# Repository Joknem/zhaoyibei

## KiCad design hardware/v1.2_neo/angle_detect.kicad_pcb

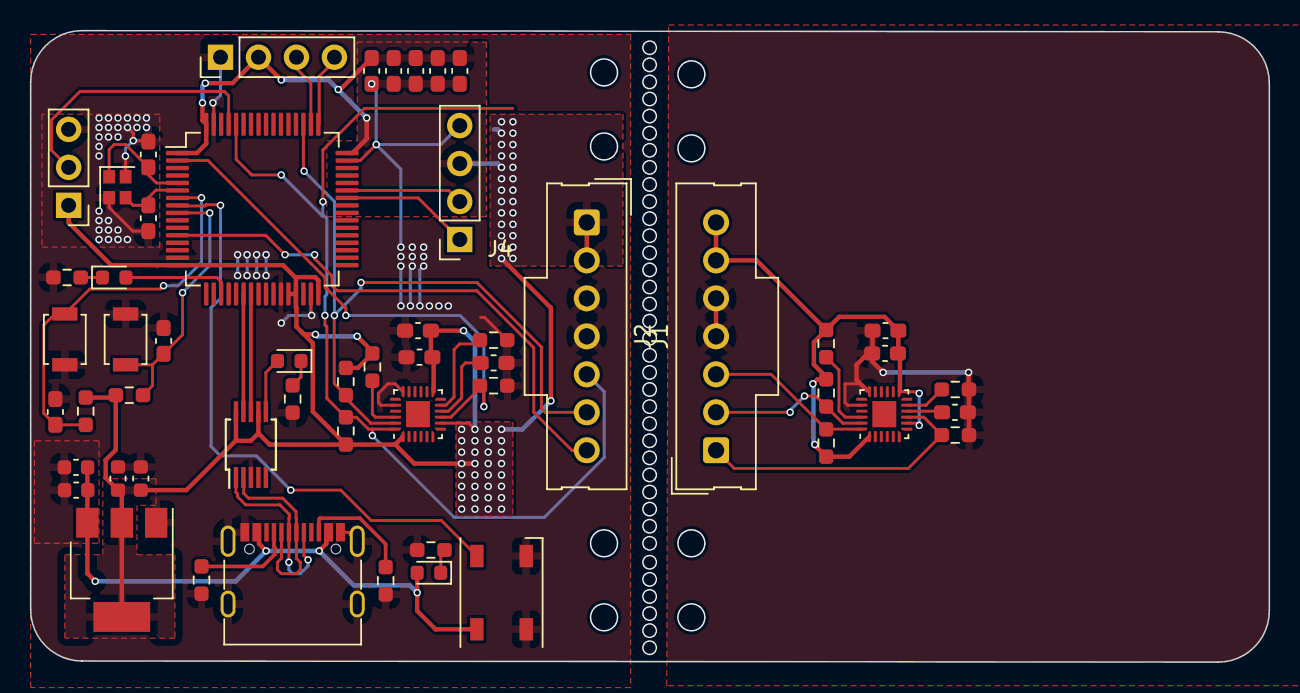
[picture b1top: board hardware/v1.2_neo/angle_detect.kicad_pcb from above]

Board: 2 copper layers, 82.9 x 42.2 mm, 54 parts (0 on the bottom side), 39 nets.

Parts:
C1, C16: 10nF; C_0603_1608Metric_Pad1.08x0.95mm_HandSolder
C2, C14, C15, C17, C18, C19: 0.1uF; C_0603_1608Metric_Pad1.08x0.95mm_HandSolder
C3, C6: 0.1uF; C_0603_1608Metric
C4, C5: 10uF; C_0603_1608Metric
C7, C8: 6.8pF; C_0603_1608Metric_Pad1.08x0.95mm_HandSolder
C9, C10, C11, C12: 100nF; C_0603_1608Metric_Pad1.08x0.95mm_HandSolder
C13: 4.7uF; C_0603_1608Metric_Pad1.08x0.95mm_HandSolder
D1: WS2812B; LED_WS2812B_PLCC4_5.0x5.0mm_P3.2mm
J1, J2: Conn_01x07; Molex_SL_171971-0007_1x07_P2.54mm_Vertical
J3: USB_C_Receptacle_USB2.0; USB_C_Receptacle_G-Switch_GT-USB-7010ASV
J4: IIC_OLED; PinSocket_1x04_P2.54mm_Vertical
J5: SWD; PinHeader_1x04_P2.54mm_Vertical
J6: Conn_01x03; PinHeader_1x03_P2.54mm_Vertical
R1, R2: 5.1k; R_0603_1608Metric_Pad0.98x0.95mm_HandSolder
R3, R4, R18: 500R; R_0603_1608Metric_Pad0.98x0.95mm_HandSolder
R5: 1k; R_0603_1608Metric_Pad0.98x0.95mm_HandSolder
R7, R8, R9, R10, R11, R12, R13, R14, R15, R16, R17: 10k; R_0603_1608Metric_Pad0.98x0.95mm_HandSolder
SW1: NRST_BUTTON; SW_SPST_B3U-1000P
SW2: USER_BUTTON; SW_SPST_B3U-1000P
U1: STM32G474RETx; LQFP-64_10x10mm_P0.5mm
U2, U3: MPU-9250; QFN-24-1EP_3x3mm_P0.4mm_EP1.75x1.6mm
U4: AMS1117-3.3; SOT-223-3_TabPin2
U5: CH340E; MSOP-10_3x3mm_P0.5mm
Y2: Crystal_GND24; Crystal_SMD_2016-4Pin_2.0x1.6mm
power_led1: LED; LED_0603_1608Metric
uart_led1: LED; LED_0603_1608Metric
user_led1: LED; LED_0603_1608Metric

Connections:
+3.3V: C5.1, C6.1, C9.1, C10.1, C11.1, C12.1, C13.1, C16.1, C18.1, J2.1, J2.2, J4.3, J5.2, J6.1, R5.1, R9.1, R11.2, R12.2, R13.2, U1.1 (VBAT), U1.16 (VDD), U1.28 (VREF+), U1.29 (VDDA), U1.32 (VDD), U1.48 (VDD), U1.64 (VDD), U3.1 (RESV_VDDIO), U3.8 (VDDIO), U3.13 (VDD), U4.2 (VO), U5.7 (VCC), U5.10 (V3)
+5V: C3.1, C4.1, D1.1 (VDD), J3.A4 (VBUS), J3.A9 (VBUS), J3.B4 (VBUS), J3.B9 (VBUS), U4.3 (VI), power_led1.2 (A)
/3.3V_B: C1.1, C2.1, J1.6, J1.7, R8.2, R10.2, R17.2, U2.1 (RESV_VDDIO), U2.8 (VDDIO), U2.13 (VDD)
/AD0: R14.2, U1.2 (PC13), U3.9 (AD0/MISO)
/AD1: J2.7, U1.12 (PA0)
/AD1_B: J1.1, R7.2, U2.9 (AD0/MISO)
/BOOT: J6.2, U1.61 (PB8)
/D+: J3.A6 (D+), J3.B6 (D+), U5.1 (UD+)
/D-: J3.A7 (D-), J3.B7 (D-), U5.2 (UD-)
/GND_B: C1.2, C2.2, C19.2, J1.4, J1.5, R7.1, R16.1, U2.18 (GND), U2.20 (RESV_GND)
/MPU_SCL: J2.6, R11.1, U1.51 (PA15), U3.23 (SCL/SCLK)
/MPU_SCL_B: J1.2, R8.1, U2.23 (SCL/SCLK)
/MPU_SDA: J2.5, R12.1, U1.60 (PB7), U3.24 (SDA/MOSI)
/MPU_SDA_B: J1.3, R10.1, U2.24 (SDA/MOSI)
/OLED_SCL: J4.2, U1.43 (PA9)
/OLED_SDA: J4.1, U1.42 (PA8)
/RX: U1.23 (PC5), U5.8 (TXD)
/SWCLK: J5.3, U1.50 (PA14)
/SWDIO: J5.4, U1.49 (PA13)
/TNOW: U5.6 (TNOW), uart_led1.2 (A)
/TX: U1.22 (PC4), U5.9 (RXD)
/USER_LED: U1.19 (PA5), user_led1.2 (A)
/rgb: D1.4 (DIN), U1.8 (PC0)
/user_button: C15.2, R9.2, SW2.1, U1.9 (PC1)
GND: C3.2, C4.2, C5.2, C6.2, C7.1, C8.1, C9.2, C10.2, C11.2, C12.2, C13.2, C14.2, C15.1, C16.2, C17.2, C18.2, D1.2 (DOUT), D1.3 (VSS), J2.3, J2.4, J3.A1 (GND), J3.A12 (GND), J3.B1 (GND), J3.B12 (GND), J3.S1 (SHIELD), J4.4, J5.1, J6.3, R1.2, R2.1, R3.2, R4.2, R14.1, R15.1, R18.2, SW1.2, SW2.2, U1.15 (VSS), U1.27 (VSSA), U1.31 (VSS), U1.47 (VSS), U1.63 (VSS), U3.18 (GND), U3.20 (RESV_GND), U4.1 (GND), U5.3 (GND), Y2.2, Y2.4
NRST: C14.1, R5.2, SW1.1, U1.7 (PG10)
unnamed: J3.A5 (CC1), R1.1
unnamed: J3.B5 (CC2), R2.2
unnamed: C7.2, U1.5 (PF0), Y2.1
unnamed: C8.2, U1.6 (PF1), Y2.3
unnamed: R16.2, U2.11 (FSYNC)
unnamed: C19.1, U2.10 (REGOUT)
unnamed: R17.1, U2.22 (~CS)
unnamed: R15.2, U3.11 (FSYNC)
unnamed: C17.1, U3.10 (REGOUT)
unnamed: R13.1, U3.22 (~CS)
unnamed: R3.1, power_led1.1 (K)
unnamed: R18.1, uart_led1.1 (K)
unnamed: R4.1, user_led1.1 (K)

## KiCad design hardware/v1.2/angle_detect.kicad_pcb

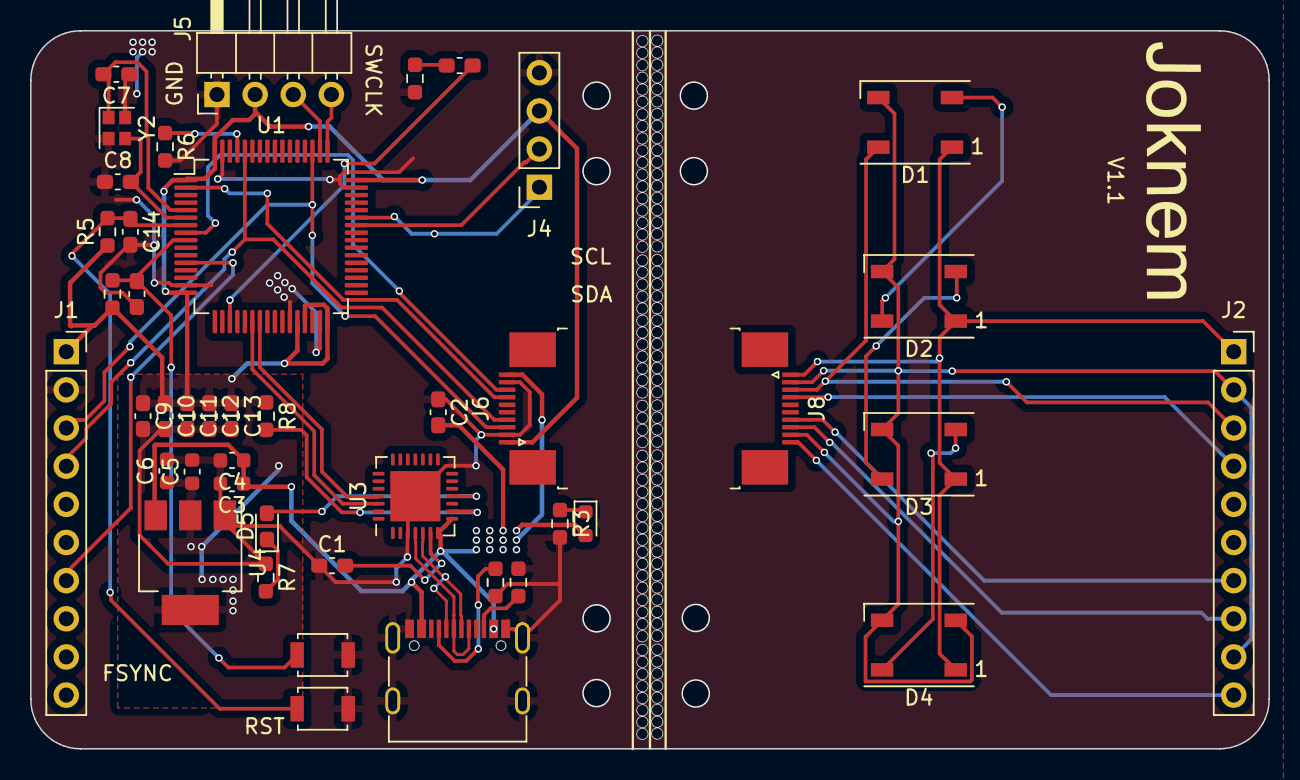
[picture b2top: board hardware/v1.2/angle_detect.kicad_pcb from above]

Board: 2 copper layers, 82.4 x 47.8 mm, 44 parts (0 on the bottom side), 40 nets.

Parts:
C1, C14, C15: 0.1uF; C_0603_1608Metric_Pad1.08x0.95mm_HandSolder
C2: 1uF; C_0603_1608Metric_Pad1.08x0.95mm_HandSolder
C3, C6: 0.1uF; C_0603_1608Metric
C4, C5: 10uF; C_0603_1608Metric
C7, C8: 6.8pF; C_0603_1608Metric_Pad1.08x0.95mm_HandSolder
C9, C10, C11, C12: 100nF; C_0603_1608Metric_Pad1.08x0.95mm_HandSolder
C13: 4.7uF; C_0603_1608Metric_Pad1.08x0.95mm_HandSolder
D1, D2, D3, D4: WS2812B; LED_WS2812B_PLCC4_5.0x5.0mm_P3.2mm
D5: uart_led; LED_0603_1608Metric_Pad1.05x0.95mm_HandSolder
J1: MPU_1; PinSocket_1x10_P2.54mm_Vertical
J2: MPU_2; PinSocket_1x10_P2.54mm_Vertical
J3: USB_C_Receptacle_USB2.0; USB_C_Receptacle_G-Switch_GT-USB-7010ASV
J4: IIC_OLED; PinSocket_1x04_P2.54mm_Vertical
J5: SWD; PinHeader_1x04_P2.54mm_Horizontal
J6: MPU_2_fpc1; TE_1-1734839-0_1x10-1MP_P0.5mm_Horizontal
J8: MPU_2_fpc2; TE_1-1734839-0_1x10-1MP_P0.5mm_Horizontal
R1, R2: 5.1k; R_0603_1608Metric_Pad0.98x0.95mm_HandSolder
R3, R4, R7: 500R; R_0603_1608Metric_Pad0.98x0.95mm_HandSolder
R5: 1k; R_0603_1608Metric_Pad0.98x0.95mm_HandSolder
R6, R9: 10k; R_0603_1608Metric_Pad0.98x0.95mm_HandSolder
R8: 4.7k; R_0603_1608Metric_Pad0.98x0.95mm_HandSolder
SW1: NRST_BUTTON; SW_SPST_B3U-1000P
SW2: USER_BUTTON; SW_SPST_B3U-1000P
U1: STM32G474RETx; LQFP-64_10x10mm_P0.5mm
U3: CP2102N-Axx-xQFN28; QFN-28-1EP_5x5mm_P0.5mm_EP3.35x3.35mm
U4: AMS1117-3.3; SOT-223-3_TabPin2
Y2: Crystal_GND24; Crystal_SMD_2016-4Pin_2.0x1.6mm
power_led1: LED; LED_0603_1608Metric
user_led1: LED; C_0603_1608Metric_Pad1.08x0.95mm_HandSolder

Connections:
+3.3V: C5.1, C6.1, C9.1, C10.1, C11.1, C12.1, C13.1, J1.1, J4.3, J5.2, J6.1, R5.1, R8.1, R9.1, U1.1 (VBAT), U1.16 (VDD), U1.28 (VREF+), U1.29 (VDDA), U1.32 (VDD), U1.48 (VDD), U1.64 (VDD), U4.2 (VO)
+5V: C2.2, C3.1, C4.1, J3.A4 (VBUS), J3.A9 (VBUS), J3.B4 (VBUS), J3.B9 (VBUS), J6.10, U3.7 (VREGIN), U3.8 (VBUS), U4.3 (VI), power_led1.2 (A)
/+3.3V_b: J2.10, J8.10
/+5V_b: D1.1 (VDD), D2.1 (VDD), D3.1 (VDD), D4.1 (VDD), J2.1, J8.1
/AD0: J1.7, U1.12 (PA0)
/AD1: J6.7, U1.2 (PC13)
/AD1_b: J2.4, J8.4
/BOOT: R6.1, U1.61 (PB8)
/D+: J3.A6 (D+), J3.B6 (D+), U3.4 (D+)
/D-: J3.A7 (D-), J3.B7 (D-), U3.5 (D-)
/GND_b: D1.3 (VSS), D2.3 (VSS), D3.3 (VSS), D4.2 (DOUT), D4.3 (VSS), J2.2, J2.9, J8.2, J8.9
/MPU_SCL: J1.3, J6.3, U1.51 (PA15)
/MPU_SCL_b: J2.8, J8.8
/MPU_SDA: J1.4, J6.4, U1.60 (PB7)
/MPU_SDA_b: J2.7, J8.7
/OLED_SCL: J4.2, U1.42 (PA8)
/OLED_SDA: J4.1, U1.43 (PA9)
/RX: U1.23 (PC5), U3.25 (RXD)
/SWCLK: J5.4, U1.49 (PA13)
/SWDIO: J5.3, U1.50 (PA14)
/TX: U1.22 (PC4), U3.26 (TXD)
/USER_LED: U1.19 (PA5), user_led1.2 (A)
/rgb: J6.8, U1.8 (PC0)
/rgb_b: D1.4 (DIN), J2.3, J8.3
/user_button: C15.2, R9.2, SW2.1, U1.9 (PC1)
GND: C1.1, C2.1, C3.2, C4.2, C5.2, C6.2, C7.1, C8.1, C9.2, C10.2, C11.2, C12.2, C13.2, C14.2, C15.1, J1.2, J3.A1 (GND), J3.A12 (GND), J3.B1 (GND), J3.B12 (GND), J3.S1 (SHIELD), J4.4, J5.1, J6.2, J6.9, R1.2, R2.1, R3.2, R4.2, R6.2, R7.1, SW1.2, SW2.2, U1.15 (VSS), U1.27 (VSSA), U1.31 (VSS), U1.47 (VSS), U1.63 (VSS), U3.3 (GND), U3.29 (GND), U4.1 (GND), Y2.2, Y2.4
NRST: C14.1, R5.2, SW1.1, U1.7 (PG10)
unnamed: D1.2 (DOUT), D2.4 (DIN)
unnamed: D2.2 (DOUT), D3.4 (DIN)
unnamed: D3.2 (DOUT), D4.4 (DIN)
unnamed: D5.2 (A), U3.11 (~SUSPEND)
unnamed: D5.1 (K), R7.2
unnamed: J3.A5 (CC1), R1.1
unnamed: J3.B5 (CC2), R2.2
unnamed: C7.2, U1.5 (PF0), Y2.1
unnamed: C8.2, U1.6 (PF1), Y2.3
unnamed: C1.2, U3.6 (VDD)
unnamed: R8.2, U3.9 (~RST)
unnamed: R3.1, power_led1.1 (K)
unnamed: R4.1, user_led1.1 (K)

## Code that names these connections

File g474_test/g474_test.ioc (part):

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Mcu.Name=STM32G474R(B-C-E)Tx
Mcu.Package=LQFP64
Mcu.UserName=STM32G474RETx
PA0.GPIOParameters=GPIO_Label
PA0.GPIO_Label=AD1
PA0.Signal=GPIO_Output
PA13.Mode=Serial_Wire
PA13.Signal=SYS_JTMS-SWDIO
PA14.Mode=Serial_Wire
PA14.Signal=SYS_JTCK-SWCLK
PA15.Mode=I2C
PA15.Signal=I2C1_SCL
PA5.GPIOParameters=GPIO_Speed,GPIO_PuPd,GPIO_Label
PA5.GPIO_Label=LED
PA5.GPIO_PuPd=GPIO_PULLUP
PA5.GPIO_Speed=GPIO_SPEED_FREQ_LOW
PA5.Signal=GPIO_Output
PA8.GPIOParameters=GPIO_Label
PA8.GPIO_Label=OLED_SDA
PA8.Mode=I2C
PA8.Signal=I2C2_SDA
PA9.GPIOParameters=GPIO_Label
PA9.GPIO_Label=OLED_SCL
PA9.Mode=I2C
PA9.Signal=I2C2_SCL
PB7.Mode=I2C
PB7.Signal=I2C1_SDA
PC0.GPIOParameters=GPIO_Label
PC0.GPIO_Label=RGB
PC0.Signal=S_TIM1_CH1
PC1.GPIOParameters=GPIO_Label
PC1.GPIO_Label=user_button
PC1.Signal=GPXTI1
PC13.GPIOParameters=GPIO_PuPd,GPIO_Label
PC13.GPIO_Label=AD0
PC13.GPIO_PuPd=GPIO_PULLDOWN
PC13.Signal=GPIO_Output
PC14-OSC32_IN.Mode=LSE-External-Oscillator
PC14-OSC32_IN.Signal=RCC_OSC32_IN
PC15-OSC32_OUT.Mode=LSE-External-Oscillator
PC15-OSC32_OUT.Signal=RCC_OSC32_OUT
PC4.Mode=Asynchronous
PC4.Signal=USART1_TX
PC5.Mode=Asynchronous
PC5.Signal=USART1_RX
PF0-OSC_IN.Mode=HSE-External-Oscillator
PF0-OSC_IN.Signal=RCC_OSC_IN
PF1-OSC_OUT.Mode=HSE-External-Oscillator
PF1-OSC_OUT.Signal=RCC_OSC_OUT
RCC.HSE_VALUE=24000000
RCC.SYSCLKFreq_VALUE=24000000
RCC.SYSCLKSource=RCC_SYSCLKSOURCE_HSE
board=custom

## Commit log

2024-04-21 raw data
2024-04-25 add dmp
2024-05-22 add hardware
2024-06-08 freertos init
2024-06-09 archetecture optimize
2024-06-09 u8g2 ok
2024-06-09 u8g2 fuck
2024-06-20 fake
